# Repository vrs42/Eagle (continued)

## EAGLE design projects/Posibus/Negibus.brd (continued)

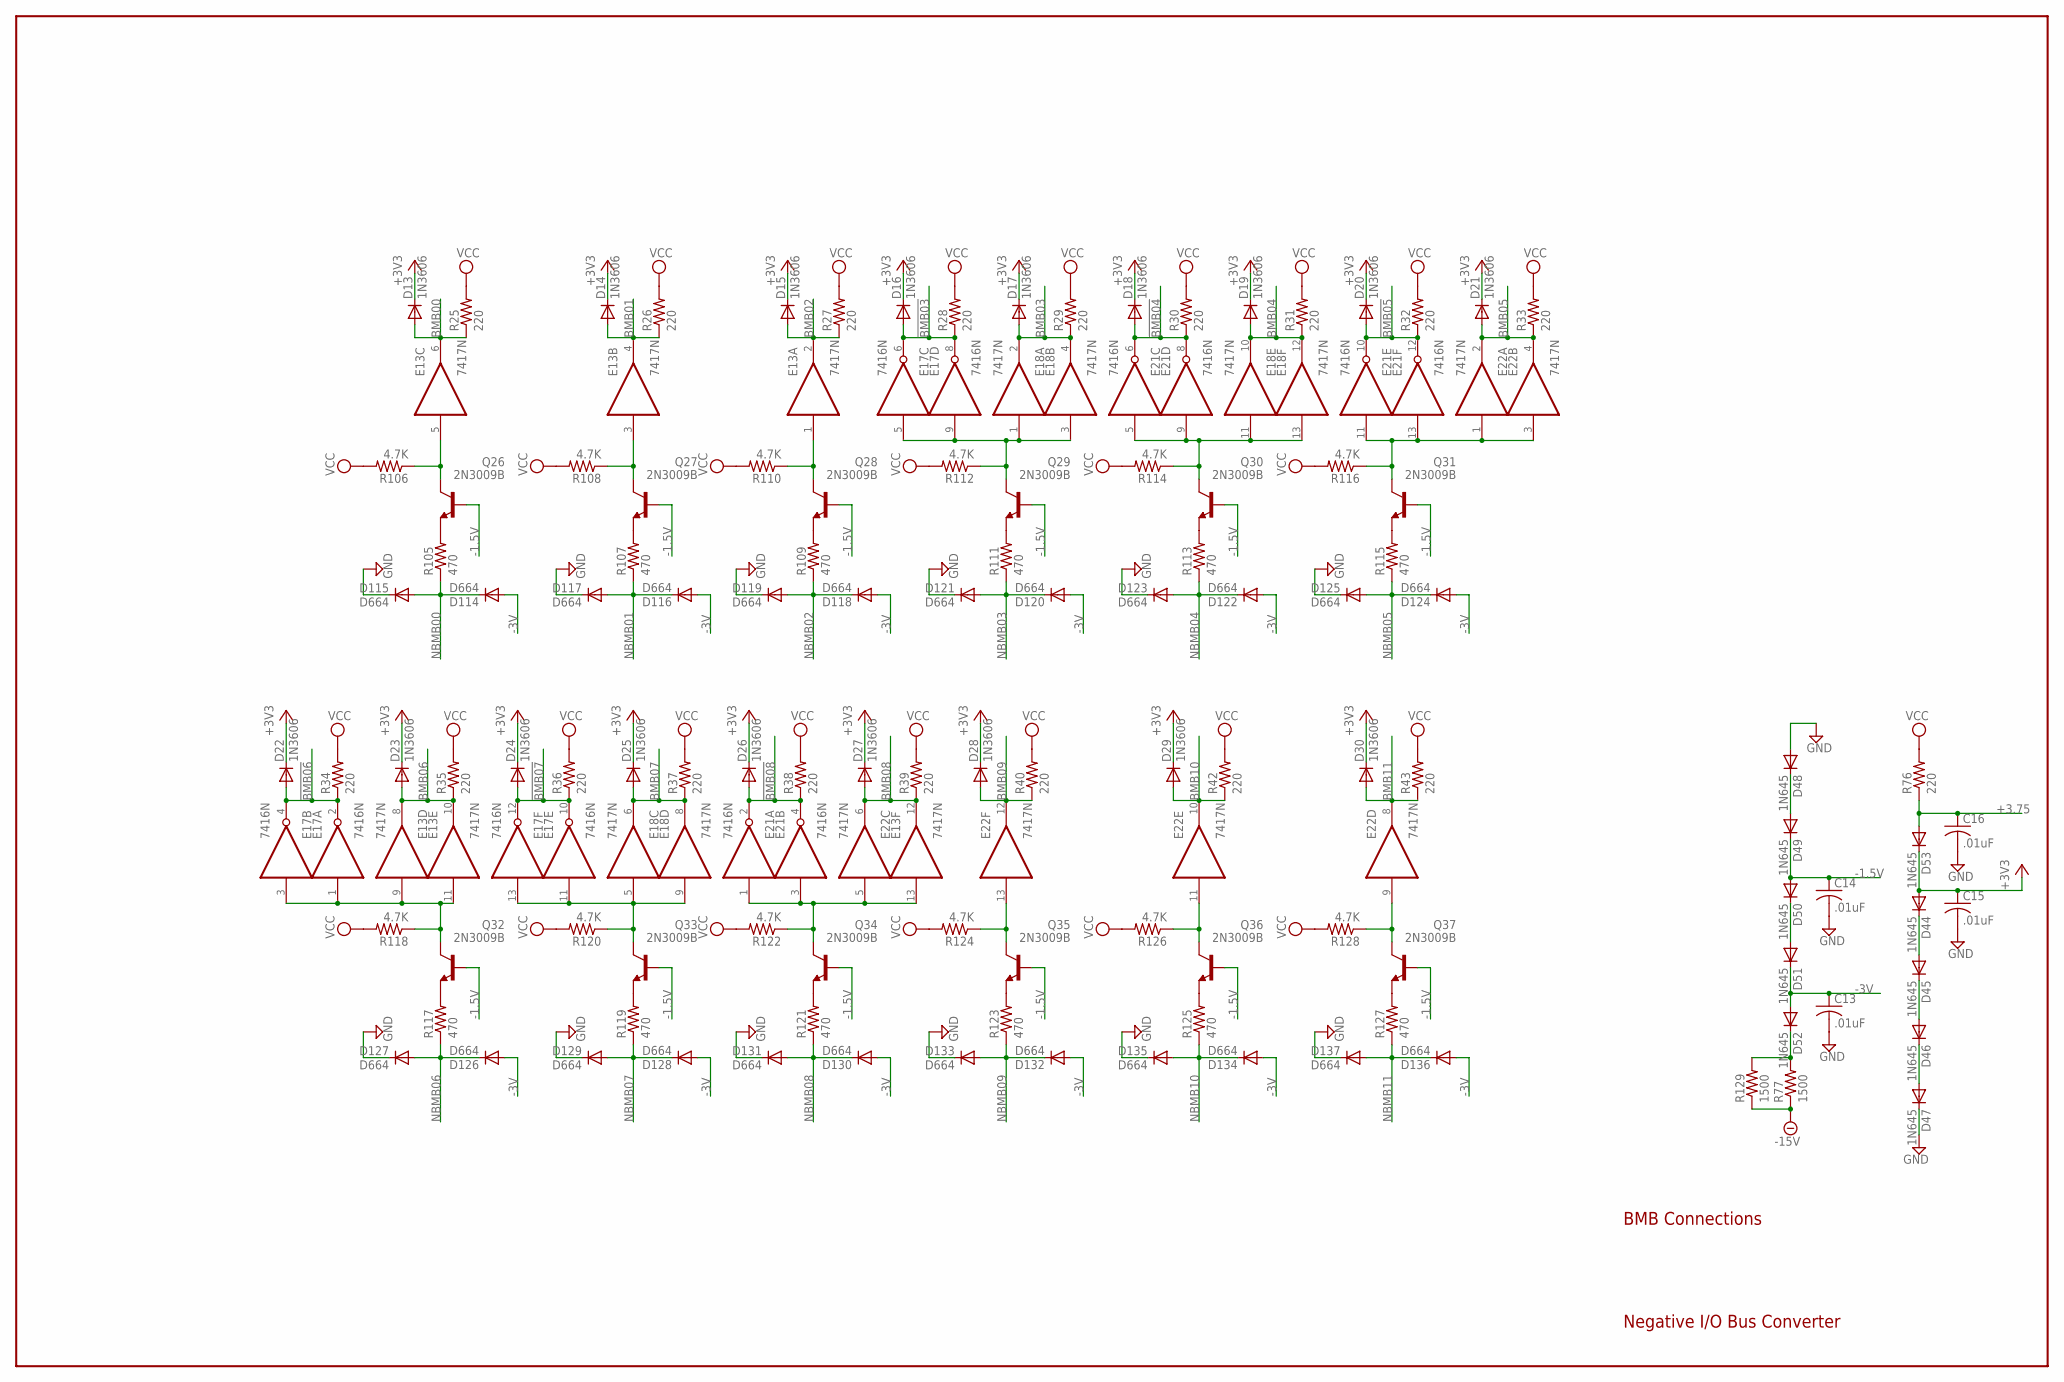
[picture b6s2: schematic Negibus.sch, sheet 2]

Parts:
C13, C14, C15, C16: .01uF; C050-025X075
D13, D14, D15, D16, D17, D18, D19, D20, D21, D22, D23, D24, D25, D26, D27, D28, D29, D30: 1N3606; DO35-10
D44, D45, D46, D47, D48, D49, D50, D51, D52, D53: 1N645; DO35-10
D114, D115, D116, D117, D118, D119, D120, D121, D122, D123, D124, D125, D126, D127, D128, D129, D130, D131, D132, D133, D134, D135, D136, D137: D664; DO35-10
E13, E18, E22: 7417N; DIL14
E17, E21: 7416N; DIL14
Q26, Q27, Q28, Q29, Q30, Q31, Q32, Q33, Q34, Q35, Q36, Q37: 2N3009B; TO39
R25, R26, R27, R28, R29, R30, R31, R32, R33, R34, R35, R36, R37, R38, R39, R40, R42, R43, R76: 220; 0207/10
R77, R129: 1500; 0207/10
R105, R107, R109, R111, R113, R115, R117, R119, R121, R123, R125, R127: 470; 0207/10
R106, R108, R110, R112, R114, R116, R118, R120, R122, R124, R126, R128: 4.7K; 0207/10

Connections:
!BMB03: D16.A, E17.6 (O), E17.8 (O), R28.1; also elsewhere on the board
!BMB04: D18.A, E21.6 (O), E21.8 (O), R30.1; also elsewhere on the board
!BMB05: D20.A, E21.10 (O), E21.12 (O), R32.1; also elsewhere on the board
!BMB06: D22.A, E17.2 (O), E17.4 (O), R34.1; also elsewhere on the board
!BMB07: D24.A, E17.10 (O), E17.12 (O), R36.1; also elsewhere on the board
!BMB08: D26.A, E21.2 (O), E21.4 (O), R38.1; also elsewhere on the board
+3.75: C16.1, D53.A, R76.1; also elsewhere on the board
+3V3: C15.1, D13.C, D14.C, D15.C, D16.C, D17.C, D18.C, D19.C, D20.C, D21.C, D22.C, D23.C, D24.C, D25.C, D26.C, D27.C, D28.C, D29.C, D30.C, D44.A, D53.C; also elsewhere on the board
-1.5V: C14.1, D49.C, D50.A, Q26.2 (B), Q27.2 (B), Q28.2 (B), Q29.2 (B), Q30.2 (B), Q31.2 (B), Q32.2 (B), Q33.2 (B), Q34.2 (B), Q35.2 (B), Q36.2 (B), Q37.2 (B); also elsewhere on the board
-3V: C13.1, D51.C, D52.A, D114.A, D116.A, D118.A, D120.A, D122.A, D124.A, D126.A, D128.A, D130.A, D132.A, D134.A, D136.A; also elsewhere on the board
-15V: R77.1, R129.1; also elsewhere on the board
BMB00: D13.A, E13.6 (O), R25.1; also elsewhere on the board
BMB01: D14.A, E13.4 (O), R26.1; also elsewhere on the board
BMB02: D15.A, E13.2 (O), R27.1; also elsewhere on the board
BMB03: D17.A, E18.2 (O), E18.4 (O), R29.1; also elsewhere on the board
BMB04: D19.A, E18.10 (O), E18.12 (O), R31.1; also elsewhere on the board
BMB05: D21.A, E22.2 (O), E22.4 (O), R33.1; also elsewhere on the board
BMB06: D23.A, E13.8 (O), E13.10 (O), R35.1; also elsewhere on the board
BMB07: D25.A, E18.6 (O), E18.8 (O), R37.1; also elsewhere on the board
BMB08: D27.A, E13.12 (O), E22.6 (O), R39.1; also elsewhere on the board
BMB09: D28.A, E22.12 (O), R40.1; also elsewhere on the board
BMB10: D29.A, E22.10 (O), R42.1; also elsewhere on the board
BMB11: D30.A, E22.8 (O), R43.1; also elsewhere on the board
GND: C13.2, C14.2, C15.2, C16.2, D47.C, D48.A, D115.C, D117.C, D119.C, D121.C, D123.C, D125.C, D127.C, D129.C, D131.C, D133.C, D135.C, D137.C, E13.7 (GND), E17.7 (GND), E18.7 (GND), E21.7 (GND), E22.7 (GND); also elsewhere on the board
unnamed: Q26.1 (E), R105.2
unnamed: E13.5 (I), Q26.3 (C), R106.1
unnamed: Q27.1 (E), R107.2
unnamed: E18.11 (I), E18.13 (I), E21.5 (I), E21.9 (I), Q30.3 (C), R114.1
unnamed: D52.C, R77.2, R129.2
unnamed: E13.3 (I), Q27.3 (C), R108.1
unnamed: Q28.1 (E), R109.2
unnamed: E13.1 (I), Q28.3 (C), R110.1
unnamed: Q29.1 (E), R111.2
unnamed: E21.11 (I), E21.13 (I), E22.1 (I), E22.3 (I), Q31.3 (C), R116.1
unnamed: E17.11 (I), E17.13 (I), E18.5 (I), E18.9 (I), Q33.3 (C), R120.1
unnamed: E13.13 (I), E21.1 (I), E21.3 (I), E22.5 (I), Q34.3 (C), R122.1
unnamed: E17.5 (I), E17.9 (I), E18.1 (I), E18.3 (I), Q29.3 (C), R112.1
unnamed: E13.9 (I), E13.11 (I), E17.1 (I), E17.3 (I), Q32.3 (C), R118.1
unnamed: Q30.1 (E), R113.2
unnamed: E22.11 (I), Q36.3 (C), R126.1
unnamed: E22.9 (I), Q37.3 (C), R128.1
unnamed: Q31.1 (E), R115.2
unnamed: Q32.1 (E), R117.2
unnamed: Q33.1 (E), R119.2
unnamed: Q34.1 (E), R121.2
unnamed: Q35.1 (E), R123.2
unnamed: Q36.1 (E), R125.2
unnamed: Q37.1 (E), R127.2
unnamed: E22.13 (I), Q35.3 (C), R124.1
unnamed: D44.C, D45.A
unnamed: D45.C, D46.A
unnamed: D46.C, D47.A
unnamed: D48.C, D49.A
unnamed: D50.C, D51.A
NBMB00: D114.C, D115.A, R105.1; also elsewhere on the board
NBMB01: D116.C, D117.A, R107.1; also elsewhere on the board
NBMB02: D118.C, D119.A, R109.1; also elsewhere on the board
NBMB03: D120.C, D121.A, R111.1; also elsewhere on the board
NBMB04: D122.C, D123.A, R113.1; also elsewhere on the board
NBMB05: D124.C, D125.A, R115.1; also elsewhere on the board
NBMB06: D126.C, D127.A, R117.1; also elsewhere on the board
NBMB07: D128.C, D129.A, R119.1; also elsewhere on the board
NBMB08: D130.C, D131.A, R121.1; also elsewhere on the board
NBMB09: D132.C, D133.A, R123.1; also elsewhere on the board
NBMB10: D134.C, D135.A, R125.1; also elsewhere on the board
NBMB11: D136.C, D137.A, R127.1; also elsewhere on the board
VCC: E13.14 (VCC), E17.14 (VCC), E18.14 (VCC), E21.14 (VCC), E22.14 (VCC), R25.2, R26.2, R27.2, R28.2, R29.2, R30.2, R31.2, R32.2, R33.2, R34.2, R35.2, R36.2, R37.2, R38.2, R39.2, R40.2, R42.2, R43.2, R76.2, R106.2, R108.2, R110.2, R112.2, R114.2, R116.2, R118.2, R120.2, R122.2, R124.2, R126.2, R128.2; also elsewhere on the board

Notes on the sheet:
Negative I/O Bus Converter
BMB Connections

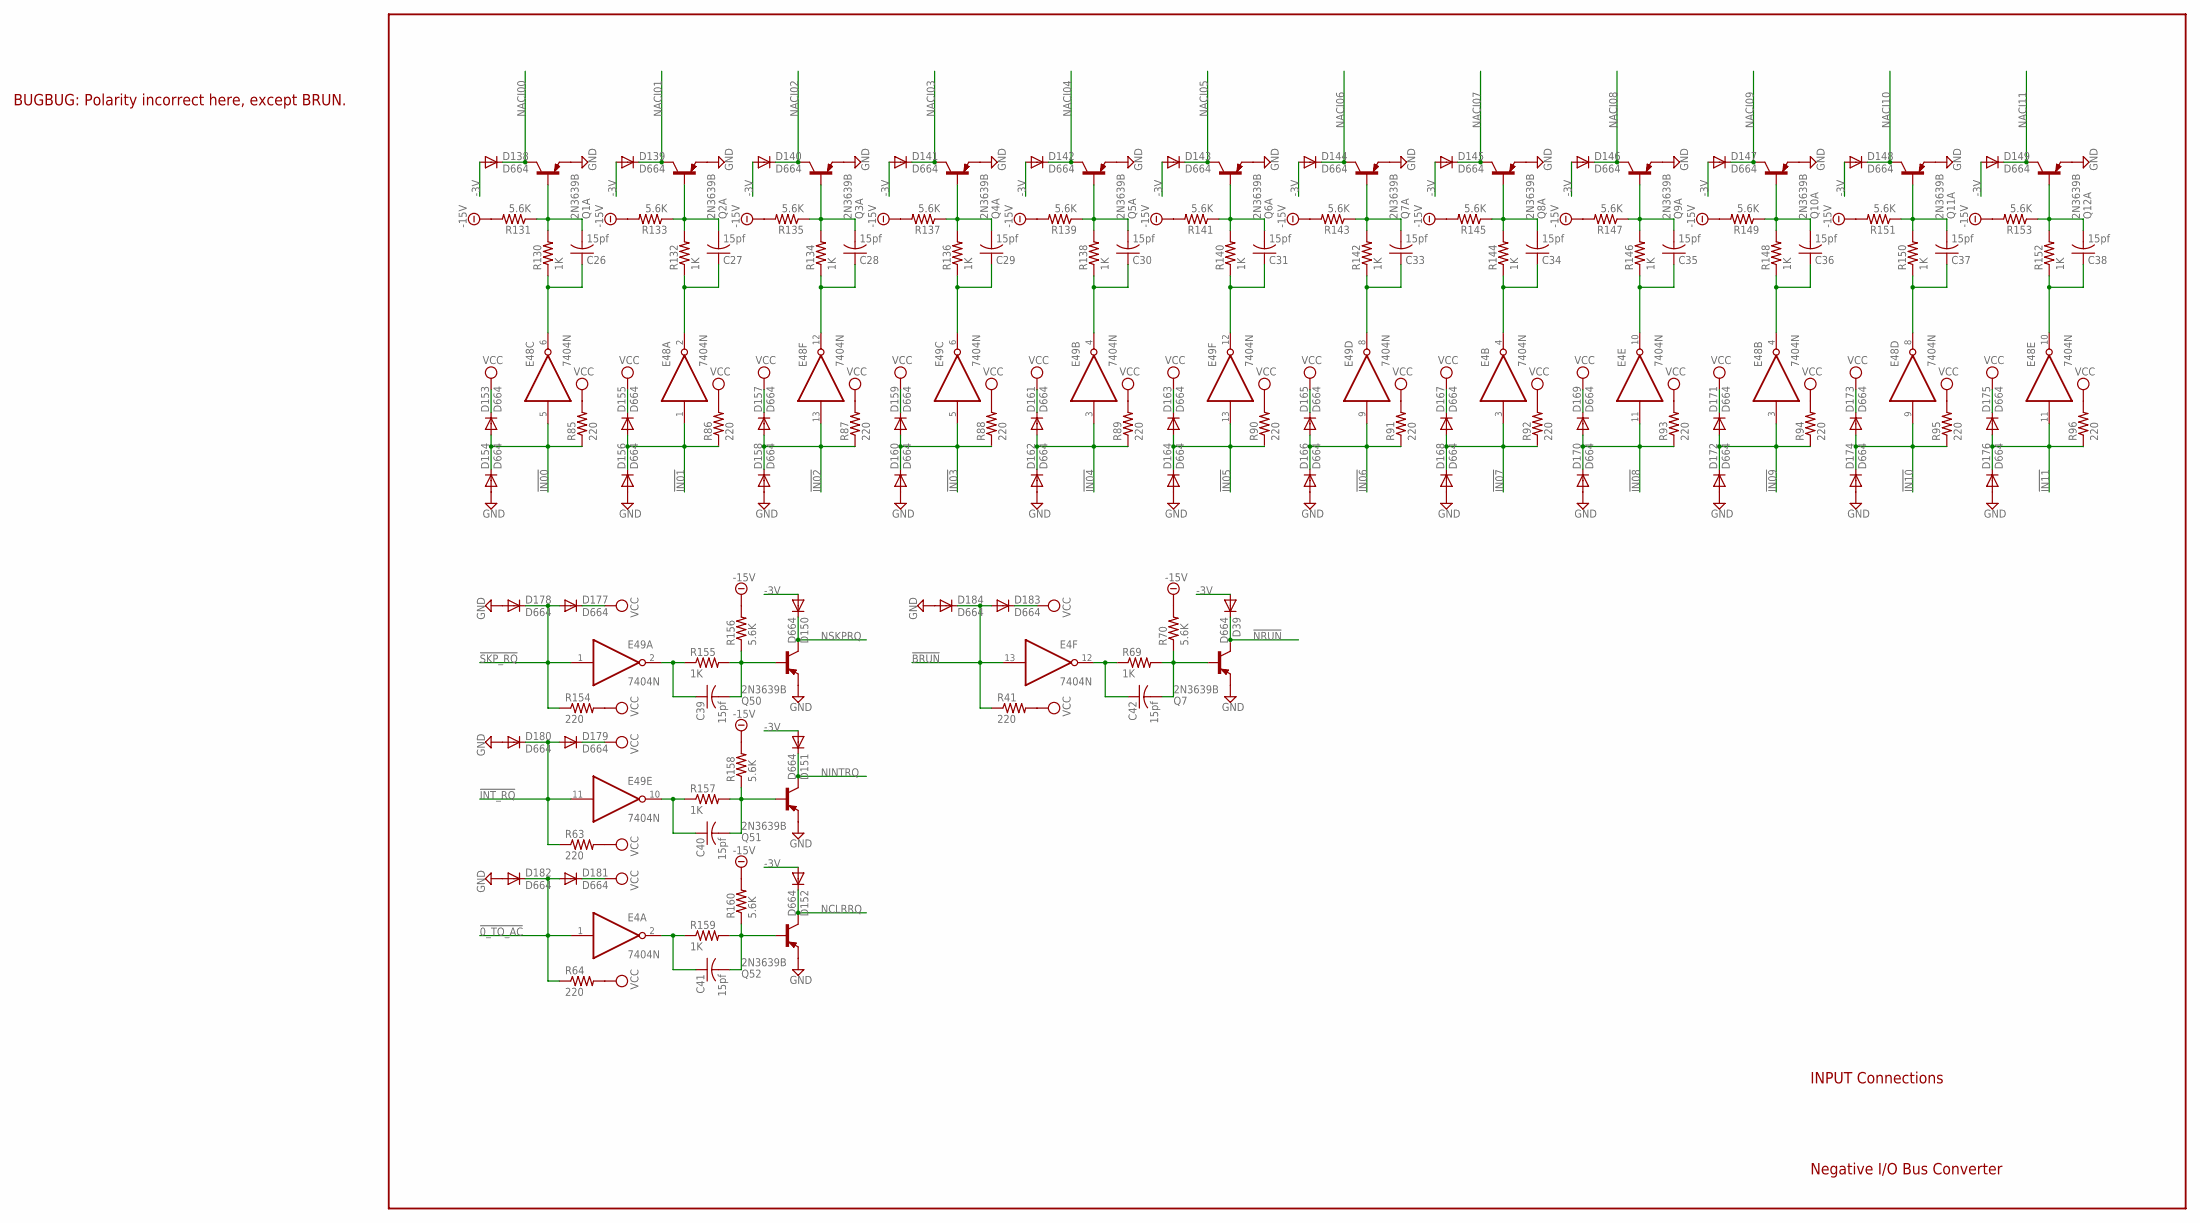
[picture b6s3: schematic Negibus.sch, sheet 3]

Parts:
C26, C27, C28, C29, C30, C31, C33, C34, C35, C36, C37, C38, C39, C40, C41, C42: 15pf; C050-025X075
D39, D138, D139, D140, D141, D142, D143, D144, D145, D146, D147, D148, D149, D150, D151, D152, D153, D154, D155, D156, D157, D158, D159, D160, D161, D162, D163, D164, D165, D166, D167, D168, D169, D170, D171, D172, D173, D174, D175, D176, D177, D178, D179, D180, D181, D182, D183, D184: D664; DO35-10
E4, E48, E49: 7404N; DIL14
Q1A, Q2A, Q3A, Q4A, Q5A, Q6A, Q7, Q7A, Q8A, Q9A, Q10A, Q11A, Q12A, Q50, Q51, Q52: 2N3639B; TO39
R41, R63, R64, R85, R86, R87, R88, R89, R90, R91, R92, R93, R94, R95, R96, R154: 220; 0207/10
R69, R130, R132, R134, R136, R138, R140, R142, R144, R146, R148, R150, R152, R155, R157, R159: 1K; 0207/10
R70, R131, R133, R135, R137, R139, R141, R143, R145, R147, R149, R151, R153, R156, R158, R160: 5.6K; 0207/10

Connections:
!0_TO_AC: D181.A, D182.C, E4.1 (I), R64.1; also elsewhere on the board
!BRUN: D183.A, D184.C, E4.13 (I), R41.1; also elsewhere on the board
!IN00: D153.A, D154.C, E48.5 (I), R85.1; also elsewhere on the board
!IN01: D155.A, D156.C, E48.1 (I), R86.1; also elsewhere on the board
!IN02: D157.A, D158.C, E48.13 (I), R87.1; also elsewhere on the board
!IN03: D159.A, D160.C, E49.5 (I), R88.1; also elsewhere on the board
!IN04: D161.A, D162.C, E49.3 (I), R89.1; also elsewhere on the board
!IN05: D163.A, D164.C, E49.13 (I), R90.1; also elsewhere on the board
!IN06: D165.A, D166.C, E49.9 (I), R91.1; also elsewhere on the board
!IN07: D167.A, D168.C, E4.3 (I), R92.1; also elsewhere on the board
!IN08: D169.A, D170.C, E4.11 (I), R93.1; also elsewhere on the board
!IN09: D171.A, D172.C, E48.3 (I), R94.1; also elsewhere on the board
!IN10: D173.A, D174.C, E48.9 (I), R95.1; also elsewhere on the board
!IN11: D175.A, D176.C, E48.11 (I), R96.1; also elsewhere on the board
!INT_RQ: D179.A, D180.C, E49.11 (I), R63.1; also elsewhere on the board
!NRUN: D39.C, Q7.3 (C); also elsewhere on the board
!SKP_RQ: D177.A, D178.C, E49.1 (I), R154.1; also elsewhere on the board
-3V: D39.A, D138.A, D139.A, D140.A, D141.A, D142.A, D143.A, D144.A, D145.A, D146.A, D147.A, D148.A, D149.A, D150.A, D151.A, D152.A; also elsewhere on the board
-15V: R70.2, R131.2, R133.2, R135.2, R137.2, R139.2, R141.2, R143.2, R145.2, R147.2, R149.2, R151.2, R153.2, R156.2, R158.2, R160.2; also elsewhere on the board
GND: D154.A, D156.A, D158.A, D160.A, D162.A, D164.A, D166.A, D168.A, D170.A, D172.A, D174.A, D176.A, D178.A, D180.A, D182.A, D184.A, E4.7 (GND), E48.7 (GND), E49.7 (GND), Q1A.1 (E), Q2A.1 (E), Q3A.1 (E), Q4A.1 (E), Q5A.1 (E), Q6A.1 (E), Q7.1 (E), Q7A.1 (E), Q8A.1 (E), Q9A.1 (E), Q10A.1 (E), Q11A.1 (E), Q12A.1 (E), Q50.1 (E), Q51.1 (E), Q52.1 (E); also elsewhere on the board
unnamed: C26.1, E48.6 (O), R130.1
unnamed: C28.1, E48.12 (O), R134.1
unnamed: C26.2, Q1A.2 (B), R130.2, R131.1
unnamed: C39.1, E49.2 (O), R155.1
unnamed: C27.1, E48.2 (O), R132.1
unnamed: C39.2, Q50.2 (B), R155.2, R156.1
unnamed: C27.2, Q2A.2 (B), R132.2, R133.1
unnamed: C40.1, E49.10 (O), R157.1
unnamed: C40.2, Q51.2 (B), R157.2, R158.1
unnamed: C28.2, Q3A.2 (B), R134.2, R135.1
unnamed: C41.1, E4.2 (O), R159.1
unnamed: C29.1, E49.6 (O), R136.1
unnamed: C29.2, Q4A.2 (B), R136.2, R137.1
unnamed: C41.2, Q52.2 (B), R159.2, R160.1
unnamed: C30.1, E49.4 (O), R138.1
unnamed: C42.1, E4.12 (O), R69.1
unnamed: C30.2, Q5A.2 (B), R138.2, R139.1
unnamed: C42.2, Q7.2 (B), R69.2, R70.1
unnamed: C31.1, E49.12 (O), R140.1
unnamed: C31.2, Q6A.2 (B), R140.2, R141.1
unnamed: C33.1, E49.8 (O), R142.1
unnamed: C34.1, E4.4 (O), R144.1
unnamed: C35.1, E4.10 (O), R146.1
unnamed: C33.2, Q7A.2 (B), R142.2, R143.1
unnamed: C38.1, E48.10 (O), R152.1
unnamed: C36.1, E48.4 (O), R148.1
unnamed: C34.2, Q8A.2 (B), R144.2, R145.1
unnamed: C37.1, E48.8 (O), R150.1
unnamed: C35.2, Q9A.2 (B), R146.2, R147.1
unnamed: C36.2, Q10A.2 (B), R148.2, R149.1
unnamed: C37.2, Q11A.2 (B), R150.2, R151.1
unnamed: C38.2, Q12A.2 (B), R152.2, R153.1
NACI00: D138.C, Q1A.3 (C); also elsewhere on the board
NACI01: D139.C, Q2A.3 (C); also elsewhere on the board
NACI02: D140.C, Q3A.3 (C); also elsewhere on the board
NACI03: D141.C, Q4A.3 (C); also elsewhere on the board
NACI04: D142.C, Q5A.3 (C); also elsewhere on the board
NACI05: D143.C, Q6A.3 (C); also elsewhere on the board
NACI06: D144.C, Q7A.3 (C); also elsewhere on the board
NACI07: D145.C, Q8A.3 (C); also elsewhere on the board
NACI08: D146.C, Q9A.3 (C); also elsewhere on the board
NACI09: D147.C, Q10A.3 (C); also elsewhere on the board
NACI10: D148.C, Q11A.3 (C); also elsewhere on the board
NACI11: D149.C, Q12A.3 (C); also elsewhere on the board
NCLRRQ: D152.C, Q52.3 (C); also elsewhere on the board
NINTRQ: D151.C, Q51.3 (C); also elsewhere on the board
NSKPRQ: D150.C, Q50.3 (C); also elsewhere on the board
VCC: D153.C, D155.C, D157.C, D159.C, D161.C, D163.C, D165.C, D167.C, D169.C, D171.C, D173.C, D175.C, D177.C, D179.C, D181.C, D183.C, E4.14 (VCC), E48.14 (VCC), E49.14 (VCC), R41.2, R63.2, R64.2, R85.2, R86.2, R87.2, R88.2, R89.2, R90.2, R91.2, R92.2, R93.2, R94.2, R95.2, R96.2, R154.2; also elsewhere on the board

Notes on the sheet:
Negative I/O Bus Converter
INPUT Connections
BUGBUG: Polarity incorrect here, except BRUN.

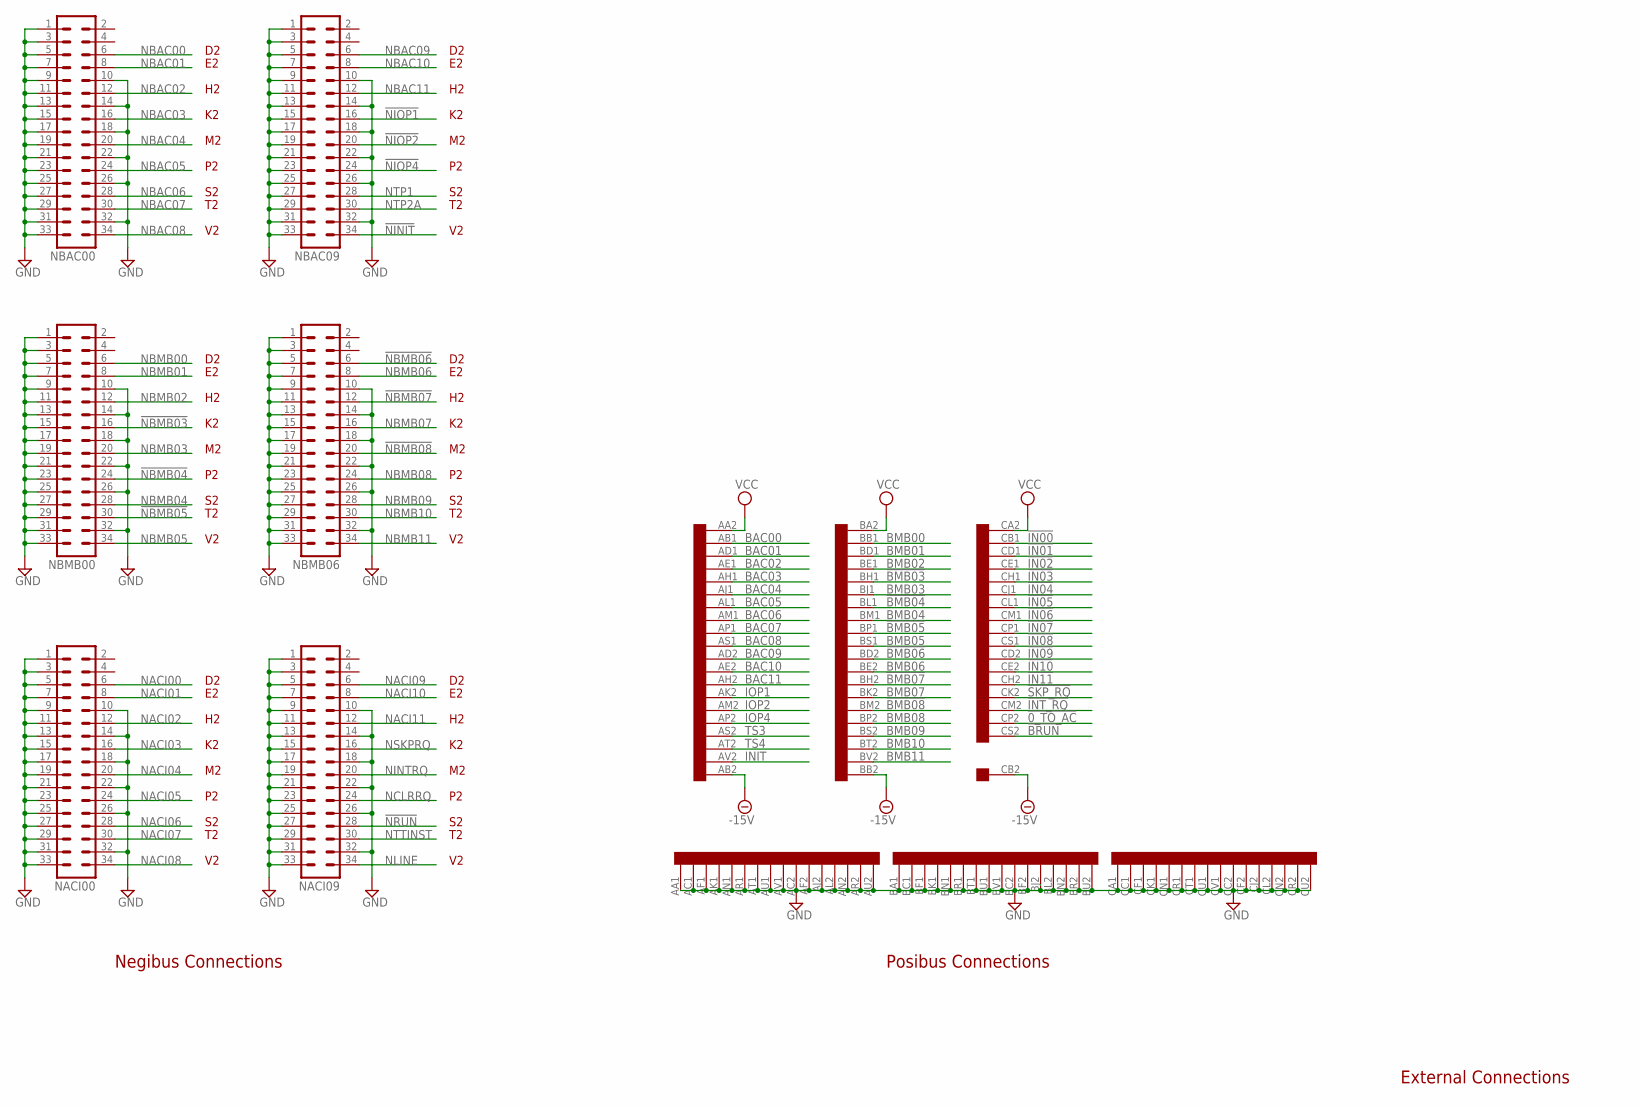
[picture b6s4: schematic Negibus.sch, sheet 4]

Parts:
NACI00, NACI09: ML34L
NBAC00, NBAC09: ML34L
NBMB00, NBMB06: ML34L
U$3: QUAD; EDGE-CON8

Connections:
!0_TO_AC: U$3.CP2; also elsewhere on the board
!BMB03: U$3.BH1; also elsewhere on the board
!BMB04: U$3.BL1; also elsewhere on the board
!BMB05: U$3.BP1; also elsewhere on the board
!BMB06: U$3.BD2; also elsewhere on the board
!BMB07: U$3.BH2; also elsewhere on the board
!BMB08: U$3.BM2; also elsewhere on the board
!BRUN: U$3.CS2; also elsewhere on the board
!IN00: U$3.CB1; also elsewhere on the board
!IN01: U$3.CD1; also elsewhere on the board
!IN02: U$3.CE1; also elsewhere on the board
!IN03: U$3.CH1; also elsewhere on the board
!IN04: U$3.CJ1; also elsewhere on the board
!IN05: U$3.CL1; also elsewhere on the board
!IN06: U$3.CM1; also elsewhere on the board
!IN07: U$3.CP1; also elsewhere on the board
!IN08: U$3.CS1; also elsewhere on the board
!IN09: U$3.CD2; also elsewhere on the board
!IN10: U$3.CE2; also elsewhere on the board
!IN11: U$3.CH2; also elsewhere on the board
!INT_RQ: U$3.CM2; also elsewhere on the board
!NBMB03: NBMB00.16
!NBMB04: NBMB00.24
!NBMB05: NBMB00.30
!NBMB06: NBMB06.6
!NBMB07: NBMB06.12
!NBMB08: NBMB06.20
!NINIT: NBAC09.34; also elsewhere on the board
!NIOP1: NBAC09.16; also elsewhere on the board
!NIOP2: NBAC09.20; also elsewhere on the board
!NIOP4: NBAC09.24; also elsewhere on the board
!NRUN: NACI09.28; also elsewhere on the board
!SKP_RQ: U$3.CK2; also elsewhere on the board
-15V: U$3.AB2, U$3.BB2, U$3.CB2; also elsewhere on the board
BAC00: U$3.AB1; also elsewhere on the board
BAC01: U$3.AD1; also elsewhere on the board
BAC02: U$3.AE1; also elsewhere on the board
BAC03: U$3.AH1; also elsewhere on the board
BAC04: U$3.AJ1; also elsewhere on the board
BAC05: U$3.AL1; also elsewhere on the board
BAC06: U$3.AM1; also elsewhere on the board
BAC07: U$3.AP1; also elsewhere on the board
BAC08: U$3.AS1; also elsewhere on the board
BAC09: U$3.AD2; also elsewhere on the board
BAC10: U$3.AE2; also elsewhere on the board
BAC11: U$3.AH2; also elsewhere on the board
BMB00: U$3.BB1; also elsewhere on the board
BMB01: U$3.BD1; also elsewhere on the board
BMB02: U$3.BE1; also elsewhere on the board
BMB03: U$3.BJ1; also elsewhere on the board
BMB04: U$3.BM1; also elsewhere on the board
BMB05: U$3.BS1; also elsewhere on the board
BMB06: U$3.BE2; also elsewhere on the board
BMB07: U$3.BK2; also elsewhere on the board
BMB08: U$3.BP2; also elsewhere on the board
BMB09: U$3.BS2; also elsewhere on the board
BMB10: U$3.BT2; also elsewhere on the board
BMB11: U$3.BV2; also elsewhere on the board
GND: NACI00.1, NACI00.3, NACI00.5, NACI00.7, NACI00.9, NACI00.10, NACI00.11, NACI00.13, NACI00.14, NACI00.15, NACI00.17, NACI00.18, NACI00.19, NACI00.21, NACI00.22, NACI00.23, NACI00.25, NACI00.26, NACI00.27, NACI00.29, NACI00.31, NACI00.32, NACI00.33, NACI09.1, NACI09.3, NACI09.5, NACI09.7, NACI09.9, NACI09.10, NACI09.11, NACI09.13, NACI09.14, NACI09.15, NACI09.17, NACI09.18, NACI09.19, NACI09.21, NACI09.22, NACI09.23, NACI09.25, NACI09.26, NACI09.27, NACI09.29, NACI09.31, NACI09.32, NACI09.33, NBAC00.1, NBAC00.3, NBAC00.5, NBAC00.7, NBAC00.9, NBAC00.10, NBAC00.11, NBAC00.13, NBAC00.14, NBAC00.15, NBAC00.17, NBAC00.18, NBAC00.19, NBAC00.21, NBAC00.22, NBAC00.23, NBAC00.25, NBAC00.26, NBAC00.27, NBAC00.29, NBAC00.31, NBAC00.32, NBAC00.33, NBAC09.1, NBAC09.3, NBAC09.5, NBAC09.7, NBAC09.9, NBAC09.10, NBAC09.11, NBAC09.13, NBAC09.14, NBAC09.15, NBAC09.17, NBAC09.18, NBAC09.19, NBAC09.21, NBAC09.22, NBAC09.23, NBAC09.25, NBAC09.26, NBAC09.27, NBAC09.29, NBAC09.31, NBAC09.32, NBAC09.33, NBMB00.1, NBMB00.3, NBMB00.5, NBMB00.7, NBMB00.9, NBMB00.10, NBMB00.11, NBMB00.13, NBMB00.14, NBMB00.15, NBMB00.17, NBMB00.18, NBMB00.19, NBMB00.21, NBMB00.22, NBMB00.23, NBMB00.25, NBMB00.26, NBMB00.27, NBMB00.29, NBMB00.31, NBMB00.32, NBMB00.33, NBMB06.1, NBMB06.3, NBMB06.5, NBMB06.7, NBMB06.9, NBMB06.10, NBMB06.11, NBMB06.13, NBMB06.14, NBMB06.15, NBMB06.17, NBMB06.18, NBMB06.19, NBMB06.21, NBMB06.22, NBMB06.23, NBMB06.25, NBMB06.26, NBMB06.27, NBMB06.29, NBMB06.31, NBMB06.32, NBMB06.33, U$3.AA1, U$3.AC1, U$3.AC2, U$3.AF1, U$3.AF2, U$3.AJ2, U$3.AK1, U$3.AL2, U$3.AN1, U$3.AN2, U$3.AR1, U$3.AR2, U$3.AT1, U$3.AU1, U$3.AU2, U$3.AV1, U$3.BA1, U$3.BC1, U$3.BC2, U$3.BF1, U$3.BF2, U$3.BJ2, U$3.BK1, U$3.BL2, U$3.BN1, U$3.BN2, U$3.BR1, U$3.BR2, U$3.BT1, U$3.BU1, U$3.BU2, U$3.BV1, U$3.CA1, U$3.CC1, U$3.CC2, U$3.CF1, U$3.CF2, U$3.CJ2, U$3.CK1, U$3.CL2, U$3.CN1, U$3.CN2, U$3.CR1, U$3.CR2, U$3.CT1, U$3.CU1, U$3.CU2, U$3.CV1; also elsewhere on the board
INIT: U$3.AV2; also elsewhere on the board
IOP1: U$3.AK2; also elsewhere on the board
IOP2: U$3.AM2; also elsewhere on the board
IOP4: U$3.AP2; also elsewhere on the board
NACI00: NACI00.6; also elsewhere on the board
NACI01: NACI00.8; also elsewhere on the board
NACI02: NACI00.12; also elsewhere on the board
NACI03: NACI00.16; also elsewhere on the board
NACI04: NACI00.20; also elsewhere on the board
NACI05: NACI00.24; also elsewhere on the board
NACI06: NACI00.28; also elsewhere on the board
NACI07: NACI00.30; also elsewhere on the board
NACI08: NACI00.34; also elsewhere on the board
NACI09: NACI09.6; also elsewhere on the board
NACI10: NACI09.8; also elsewhere on the board
NACI11: NACI09.12; also elsewhere on the board
NBAC00: NBAC00.6; also elsewhere on the board
NBAC01: NBAC00.8; also elsewhere on the board
NBAC02: NBAC00.12; also elsewhere on the board
NBAC03: NBAC00.16; also elsewhere on the board
NBAC04: NBAC00.20; also elsewhere on the board
NBAC05: NBAC00.24; also elsewhere on the board
NBAC06: NBAC00.28; also elsewhere on the board
NBAC07: NBAC00.30; also elsewhere on the board
NBAC08: NBAC00.34; also elsewhere on the board
NBAC09: NBAC09.6; also elsewhere on the board
NBAC10: NBAC09.8; also elsewhere on the board
NBAC11: NBAC09.12; also elsewhere on the board
NBMB00: NBMB00.6; also elsewhere on the board
NBMB01: NBMB00.8; also elsewhere on the board
NBMB02: NBMB00.12; also elsewhere on the board
NBMB03: NBMB00.20; also elsewhere on the board
NBMB04: NBMB00.28; also elsewhere on the board
NBMB05: NBMB00.34; also elsewhere on the board
NBMB06: NBMB06.8; also elsewhere on the board
NBMB07: NBMB06.16; also elsewhere on the board
NBMB08: NBMB06.24; also elsewhere on the board
NBMB09: NBMB06.28; also elsewhere on the board
NBMB10: NBMB06.30; also elsewhere on the board
NBMB11: NBMB06.34; also elsewhere on the board
NCLRRQ: NACI09.24; also elsewhere on the board
NINTRQ: NACI09.20; also elsewhere on the board
NLINE: NACI09.34
NSKPRQ: NACI09.16; also elsewhere on the board
NTP1: NBAC09.28; also elsewhere on the board
NTP2A: NBAC09.30; also elsewhere on the board
NTTINST: NACI09.30
TS3: U$3.AS2; also elsewhere on the board
TS4: U$3.AT2; also elsewhere on the board
VCC: U$3.AA2, U$3.BA2, U$3.CA2; also elsewhere on the board

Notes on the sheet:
External Connections
Negibus Connections
Posibus Connections

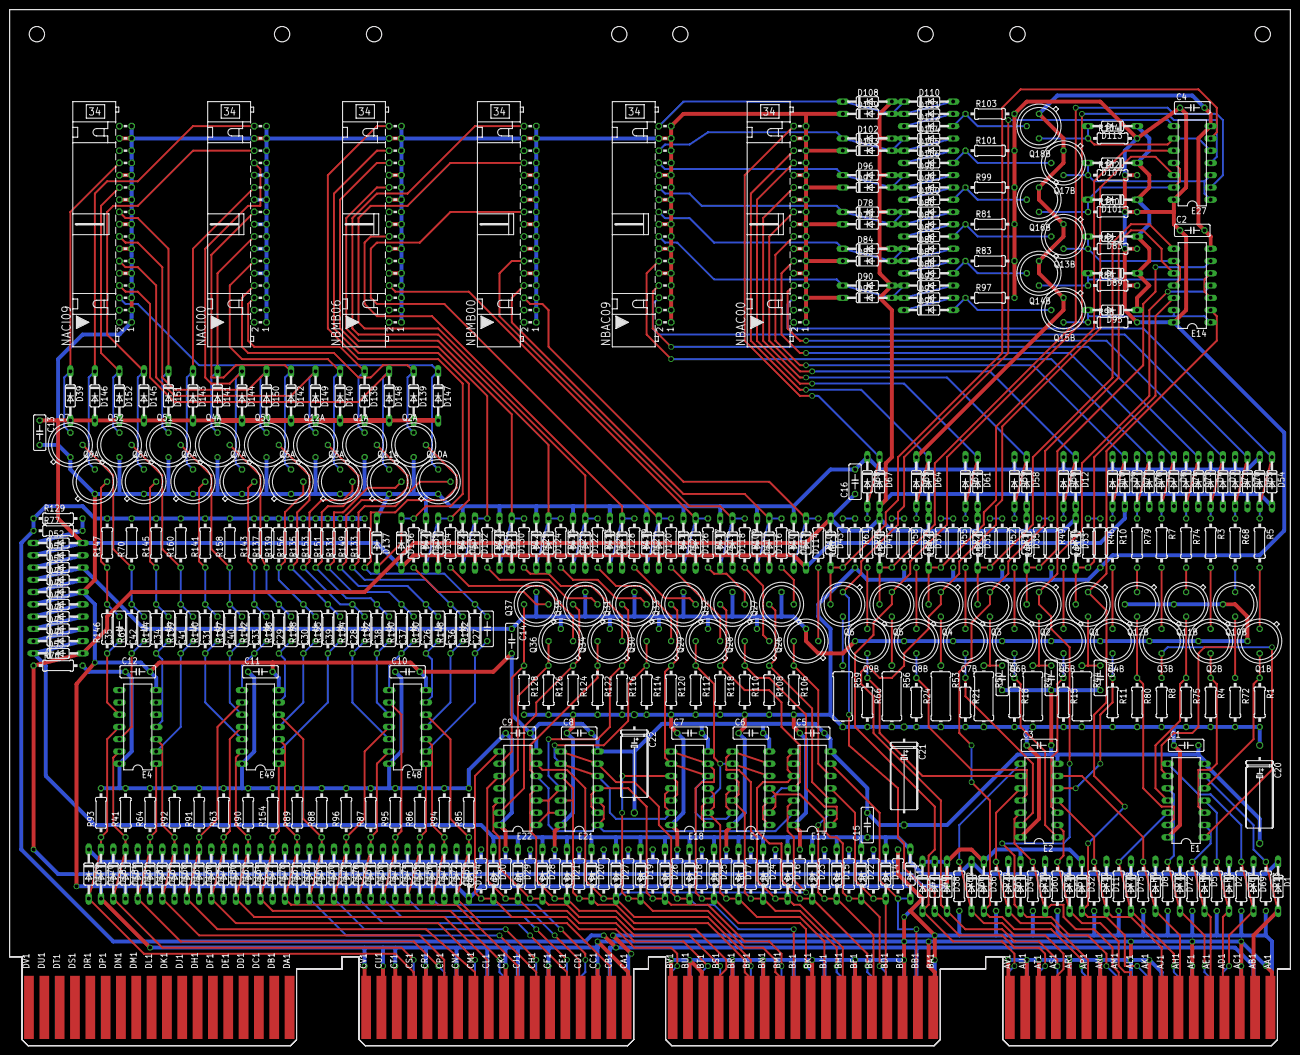
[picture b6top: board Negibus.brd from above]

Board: 2 copper layers, 265.3 x 214.6 mm, 453 parts (0 on the bottom side), 234 nets.
